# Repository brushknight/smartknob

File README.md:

# ⚠️⚠️⚠️ This repo is archived, check for updates at [@seedlabs-it](https://github.com/seedLabs-it/) 

# SmartKnob
SmartKnob is an open-source input device with software-configurable endstops and virtual detents.

A brushless gimbal motor is paired with a magnetic encoder to provide closed-loop torque feedback control, making it
possible to dynamically create and adjust the feel of detents and endstops.

Join the [Discord community](https://discord.gg/5jyhjcbTnR) to discuss the project with others, show off your build, or help answer each others' questions!

# Designs

## SmartKnob View
The "SmartKnob View" is the premium SmartKnob experience with an integrated display shown in my [demo video](https://www.youtube.com/watch?v=ip641WmY4pA). Under active development.

🎉 **Motors are [now available](https://www.sparkfun.com/products/20441)!** If you've been following this project,
you'll know that the recommended motors went out of stock nearly immediately after it was published.
Thanks to [the community](https://github.com/scottbez1/smartknob/issues/16#issuecomment-1094482805%5D), we were able to
identify the likely original manufacturer, and recently SparkFun Electronics has been getting them produced and regularly
[stocking them](https://www.sparkfun.com/products/20441)! (However, they've been selling out quickly each time they restock, so definitely sign up for backorder notifications if they're out of stock when you check). Thanks to everyone who helped search and investigate different
motor options along the way!

Features:
 - 240x240 round LCD ("GC9A01"), protected by 39.5mm watch glass on rotor
 - BLDC gimbal motor, with a hollow shaft for mechanically & electrically connecting the LCD
 - Powered by ESP32-PICO-V3-02 (Lilygo TMicro32 Plus module)
 - PCB flexure and SMD resistors used as strain gauges for press detection (haptic feedback provided via the motor)
 - 8 side-firing RGB LEDs (SK6812-SIDE-A) illuminate ring around the knob
 - USB-C (2.0) connector for 5V power and serial data/programming (CH340)
 - VEML7700 ambient light sensor for automatic backlight & LED intensity adjustment
 - Versatile back plate for mounting - use either 4x screws, or 2x 3M medium Command strips (with cutouts for accessing removal tabs after installation)
 - Front cover snaps on for easy access to the PCB

**Current status:** Not recommended for general use, but may be a fun project for an advanced electronics hobbyist.

### Demo video

### How it works

### 3D CAD

Latest Fusion 360 Model: https://a360.co/3BzkU0n

#### DEMO: video editor timeline control

If you edit audio/video, imagine having a jog wheel where you could _feel_ the clip boundaries as you scrolled through the timeline. Then switch to playback speed control, with a wheel that's spring-loaded to return to "paused," with snaps at 1x, 2x, 4x, etc. The SmartKnob can do this; it just needs some software integrations to be written. Check out a demo using a SmartKnob prototype to control a mock video timeline:

(you can actually try this demo yourself if you've already built a SmartKnob; plug it in over USB and go to https://scottbez1.github.io/smartknob/)

### Build your own?

While this is a "DIY" open-source project, it is not yet a mature plug-and-play project. If you intend to build your own, note that it requires advanced soldering experience to build - very small-pitch surface-mount soldering is required (reflow or hot air recommended), and assembly is quite time-consuming and delicate. Please go into it with the expectation that you will almost certainly need to be able to troubleshoot some hardware and firmware issues yourself - I recommend reviewing/understanding the schematics and basic firmware before jumping in!

More documentation on the BOM and what parts you need to order is coming in the future - thanks so much for your interest! Follow me on [Twitter](https://twitter.com/scottbez1) for the latest updates on this and other projects.

View the latest auto-generated (untested) [Base PCB Interactive BOM](https://smartknob-artifacts.s3.us-west-1.amazonaws.com/master/electronics/view_base-ibom.html) and [Screen PCB Interactive BOM](https://smartknob-artifacts.s3.us-west-1.amazonaws.com/master/electronics/view_screen-ibom.html) (or, the combined [BOM csv](https://smartknob-artifacts.s3.us-west-1.amazonaws.com/master/electronics/view_base-bom.csv)) for electronics/hardware parts list. ⚠️ These are auto-generated from the latest untested revision on GitHub. For tested/stable/recommended artifacts, use a [release](https://github.com/scottbez1/smartknob/releases) instead.

A few miscellaneous notes in the meantime:

 - There's limited space inside the LCD mount for wiring, and 8 wires need to fit through the hole in the center. I used 30 AWG wire-wrapping wire. Enamel-coated wire would probably work too.
 - Older versions of the design (as seen in the videos) used glued-on BF350-3AA strain gauges to detect presses; in v0.5 these were replaced with footprints for SMD resistors, which exhibit similar properties when stretched/compressed and are much easier to assemble. 
 - The TMC6300 is _tiny_ and has a bottom pad, so I would seriously consider getting a stencil along with the PCB order. Even with the stencil I needed to manually clean up some bridging afterward; I _highly_ recommend Chip Quik NC191 gel flux, available on [Amazon](https://amzn.to/3MGDSr5) (or use this [non-affiliate link](https://www.amazon.com/Smooth-Flow-No-Clean-syringe-plunger/dp/B08KJPG3NZ) instead) or from your electronics distributor of choice. Flux is also very helpful when soldering the LCD ribbon cable to to screen PCB.
 - For breadboard prototyping, the [TMC6300-BOB](https://www.trinamic.com/support/eval-kits/details/tmc6300-bob/) or SparkFun's [TMC6300 driver board](https://www.sparkfun.com/products/21867) are awesome and way easier to work with than the bare chip if you just want to play around with low current BLDC motors
 - For AliExpress purchases: I highly recommend **only** using AliExpress Standard Shipping (purchasing in the US). I have had multiple purchases take months or never get delivered when purchased with Cainiao or other low cost shipping options, whereas AliExpress Standard is very reliable and generally faster in my experience.
 - Make sure to check the [open issues](https://github.com/scottbez1/smartknob/issues) - this design is not yet "stable", so beware that everything may not go smoothly.

Future plans:
 - consider switch to using an ESP32-S3-MINI-1 module
 - get wifi configured and working (probably MQTT?). Currently memory is an issue with the full display framebuffer sprite. PSRAM might fix this (requires newer ESP-IDF & unreleased Arduino core, and from a brief test I got horrible performance with PSRAM enabled), or the next item might help reduce memory:
 - migrate to LVGL, for better display rendering and easy support for menus, etc. Shouldn't require a full 240x240x24b framebuffer in memory, freeing some for wifi, etc.
 - Home Assistant integration, or other real-world applications
 - ???
 - [Profit](https://github.com/sponsors/scottbez1/) 😉

#### Already built one?
Check out the [firmware/software documentation](https://paper.dropbox.com/doc/SmartKnob-firmware-and-software--B_oWj~L1dXqHgAqqYmhwwuqzAg-VUb9nq7btuhnHw5KlgJIH)
for tips on getting it programmed and hooking it up to your own software integrations.

If you've already uploaded the standard firmware and gone through the calibration process (see guide linked above if you don't know what this means),
go to https://scottbez1.github.io/smartknob/ to try out an interactive web-based demo that uses Web Serial to talk to a SmartKnob that's plugged into your
computer's USB port!

#### Base PCB

Ordering notes: use white soldermask, for reflecting light from RGB LED ring around the knob. Should be 1.2mm thick (not "standard" 1.6mm).

If you are ordering a stencil for solder paste from JLCPCB and plan to apply paste by hand (as
[shown in the video](https://youtu.be/Q76dMggUH1M?t=372)) without a stencil frame/machine, make sure to select
**"Customized size"** and enter smaller dimensions (e.g. 100mm x 100mm) to avoid getting a much larger stencil than you
need. This will also likely reduce the cost of shipping substantially! Also, select only the **Top** side; the bottom
only has 2 SMT components - the motor connector and VEML7700 ALS - so it's not worth getting a stencil for that.

Latest auto-generated (untested and likely broken!) artifacts⚠️:

[Schematic](https://smartknob-artifacts.s3.us-west-1.amazonaws.com/master/electronics/view_base-schematic.pdf)

[Interactive BOM](https://smartknob-artifacts.s3.us-west-1.amazonaws.com/master/electronics/view_base-ibom.html)

[PCB Packet](https://smartknob-artifacts.s3.us-west-1.amazonaws.com/master/electronics/view_base-pcb-packet.pdf)

[Gerbers](https://smartknob-artifacts.s3.us-west-1.amazonaws.com/master/electronics/view_base-jlc/gerbers.zip)

⚠️ For tested/stable/recommended artifacts, use a [release](https://github.com/scottbez1/smartknob/releases) instead.

#### Screen PCB

Ordering notes: Must be 1.2mm thick (not "standard" 1.6mm) per mechanical design. (The PCB silkscreen mentions 0.6mm thickness - this is the thickness of the **VHB tape** for adhering the LCD; the PCB should be 1.2mm thick)

There are few enough components on the Screen PCB that I chose to hand-solder them rather than reflow with solder paste
and a stencil, but if you order a stencil, see the note above about selecting a "Customized size" to be easier to
handle and save on shipping. Also make sure to select the **Bottom** side only; all the components are on the bottom
side of the screen PCB.

Latest auto-generated (untested and likely broken!) artifacts⚠️:

[Schematic](https://smartknob-artifacts.s3.us-west-1.amazonaws.com/master/electronics/view_screen-schematic.pdf)

[Interactive BOM](https://smartknob-artifacts.s3.us-west-1.amazonaws.com/master/electronics/view_screen-ibom.html)

[PCB Packet](https://smartknob-artifacts.s3.us-west-1.amazonaws.com/master/electronics/view_screen-pcb-packet.pdf)

[Gerbers](https://smartknob-artifacts.s3.us-west-1.amazonaws.com/master/electronics/view_screen-jlc/gerbers.zip)

⚠️ For tested/stable/recommended artifacts, use a [release](https://github.com/scottbez1/smartknob/releases) instead.

#### Printed parts
You will need six printed parts. The current stable designs can be found as STL assets in the [v185 mechanical release](https://github.com/scottbez1/smartknob/releases/tag/releases%2Fmechanical%2Fv185-dummy-tag) or you can export the latest untested designs from the CAD model by opening it in Fusion 360: https://a360.co/3BzkU0n

The parts can _probably_ be FDM 3D printed with a well-tuned printer, but the parts shown in videos/photos were MJF printed in nylon for tight tolerances and better surface finish. 

If you wanted a simpler build, you could omit the LCD and just merge the knob + glass from the model into a single STL to get a closed-top knob.

Export and print the following 6 parts:
* `Enclosure`
* `Knob` (RotorAssembly->KnobAssembly->Knob)
* `ScreenPlatform`
* `RotorSpacer` (RotorAssembly->RotorSpacer)
* `MountBase`
* `BackPlate`

⚠️ If you opt to go for MJF Nylon printing from JLCPCB, their system may complain about `< 0.8mm wall thickness detected` on the `MountBase`, `ScreenPlatform` and `RotorSpacer` parts. This appears to be a false positive, possibly on some of the print tapers. You should be able to ignore this, as all print orders at JLCPCB are subject to a final manual review, and they will contact you by email if there are any job-stopping issues or risks with your prints.

## NanoFOC (3rd party)
If you're looking to tinker with FOC/haptic feedback, but don't want to build a full SmartKnob View yourself, I can
recommend the NanoFOC DevKit++, an [open-source design](https://github.com/katbinaris/nanofoc_devkit) made and
[sold](https://store.binaris.io/products/nanofoc-devkit) by a member of the SmartKnob community! It's super compact
and is a great testbed or core for building your own BLDC-based haptic input device.

The NanoFOC uses an ESP32-S3, and the SmartKnob firmware works on it out of the box; just select the `nanofoc`
environment in PlatformIO rather than the `view` environment when uploading.

# Frequently Asked Questions (FAQ)

### Can I use this cheap gimbal BLDC motor I found on AliExpress?

I can't stop you, but I will caution that **you probably won't be super happy with it** depending on your intended application.

Nearly every off-the-shelf BLDC gimbal motor that the community has tested (which is pretty much ALL the cheap ones you'll find on AliExpress, trust me) has
_moderate to severge cogging_. That means the motor wants to snap to certain positions by itself even when unpowered. This means you won't be able to get
completely smooth rotation when virtual detents are turned off, and the motor's cogging may interfere with or overpower the virtual detents, particularly if
you set them to lower strength or make then very fine-grained.

The recommended motor is definitely the best (i.e. lowest cogging) off-the-shelf motor we've come across so far, and is the only readily-available motor
that I would consider "good" for this application.

If you've found another motor that is completely smooth when unpowered, we'd LOVE to hear about it in the discord; if you're wondering about some cheap motor
you saw online, either just order one and try it for yourself, or ask about it in discord but don't be surprised (or offended) if the response you get is
something terse like "nope, no good".

### How much does it cost?

I wish I could tell you now, but I don't actually know off the top of my head. Check back soon - I've only built a few so far, which was the result of a bunch of tinkering and prototyping over an extended period, so I don't have all the expenses tallied up yet. Probably less than $200 in parts? But some items have gotten more expensive, and you may be limited by minimum order quantities or shipping charges from multiple separate suppliers.

### Does it work with XYZ?

Not yet, regardless of whatever "XYZ" you're thinking of. So far I've only implemented enough firmware for the demo shown in the video, so you can't actually use it for anything productive yet. The basic detent configuration API is there, but not much else. Lots of firmware work remains to be done. If you build one, I'd love your help adding support for "XYZ" though!

### Can I buy one as a kit or already assembled?

Probably not? Or at least, I don't have any immediate plans to sell them myself. It's not that I don't want you to be happy, but hardware is a hard business and I just work on this stuff in my free time.

It's open source with a fairly permissive license though, so in theory anyone could start offering kits/assemblies. If someone does go down that route of selling them, note that attribution is
 _required_ (and I wouldn't say no to [royalties/tips/thanks](https://github.com/sponsors/scottbez1/) if you're in a giving mood 🙂).

# Firmware and Software
More extensive documentation of the firmware and software (and how to get started) can be found in the dedicated [SmartKnob Firmware and Software Guide](https://paper.dropbox.com/doc/SmartKnob-firmware-and-software--Byho6npe9XvZLZLxJ_8bK5TqAg-VUb9nq7btuhnHw5KlgJIH#:h2=Calibration)

## General Component Info

### Magnetic encoders

#### MT6701 (MagnTek)
Excellent sensor at a reasonable price - highly recommended. Less noisy than TLV493D, and more responsive (control loop is more stable) using SSI.

 - Lots of IO options - SSI, I2C, and ABZ - should offer good response latency
 - SSI includes CRC to validate data
 - No power-down or low-power options - may not be ideal for battery-powered devices
 - Not available from US distributors (Mouser, Digi-Key)

[Datasheet](http://www.magntek.com.cn/upload/MT6701_Rev.1.5.pdf)

[Ordering (LCSC)](https://lcsc.com/product-detail/Angle-Linear-Position-Sensors_Magn-Tek-MT6701CT-STD_C2856764.html)

#### TLV493D (Infineon)
Not used in the SmartKnob view, but a common/popular magnetic encoder in general. It's a mediocre choice for a haptic feedback implementation. Easy to prototype with using [Adafruit's QWIIC breakout board](https://www.adafruit.com/product/4366).

In my testing, it's noisy, requiring filtering/smoothing that can slow responsiveness, hurting control loop stability. Or, with less filtering, the noise
can easily be "amplified" by the derivative component in the PID motor torque controller, causing audible (and tactile) humming/buzzing.

But the bigger issue is that there is apparently a known silicon issue that causes the internal ADC to sometimes completely lock up, requiring a full reset and re-configuration, which can cause delays/gaps in data! See section
5.6 in the [User Manual](https://www.infineon.com/dgdl/Infineon-TLV493D-A1B6_3DMagnetic-UM-v01_03-EN.pdf?fileId=5546d46261d5e6820161e75721903ddd)

    In the Master Controlled Mode (MCM) or the Fast Mode (FM) the ADC conversion may hang up. A hang up can
    be detected by:
     - Frame Counter (FRM) counter stucks and does not increment anymore.

In my experience testing 4 different Adafruit breakout boards, 2 of them (50%) regularly exhibit this lockup behavior within a minute or two of use. It is possible to detect and auto-reset (and there is code in the project to do so), but it is slow and may cause undesirable jumps/delays if the sensor locks up often.

[Datasheet](https://www.mouser.com/datasheet/2/196/Infineon_TLV493D_A1B6_DataSheet_v01_10_EN-1227967.pdf)

#### AS5600 (AMS)
A mediocre choice. Cheap breakout boards are readily available.

In my testing, it's fairly noisy (anecdotally, noisier than the TLV493d), requiring filtering/smoothing that can slow responsiveness, hurting control loop stability. Additionally, it saturates at a lower magnetic field strength than other sensors I tested, requiring a significant air gap (8-10mm) when used with a strong neodymium diametric magnet like [Radial Magnets 8995](https://www.digikey.com/en/products/detail/radial-magnets-inc/8995/5126077).

[Datasheet](https://ams.com/documents/20143/36005/AS5600_DS000365_5-00.pdf)

### Motor drivers
#### TMC6300-LA
This is a relatively new IC and it's a perfect match! There generally aren't any other drivers (with integrated fets) that meet the requirements for the low-voltage and low-current motors used in this project (DRV8316 might work, but has not been tested).

Highlights:
 - 2-11V DC motor supply input
 - Up to 1.2A RMS
 - Tiny (3x3mm QFN)

 [Datasheet](https://www.trinamic.com/fileadmin/assets/Products/ICs_Documents/TMC6300_datasheet_rev1.07.pdf)

 [Product page](https://www.trinamic.com/products/integrated-circuits/details/tmc6300-la/)

### Motors
#### 32mm Rotor, Hollow Shaft, Diametric magnet

- 32mm rotor
- 15mm overall height (including magnet), 12.75mm height w/o magnet, 9mm rotor height
- low/zero cogging - excellent for completely smooth input
- 5.9mm hollow shaft
- built-in diametric magnet for encoder
- Proven option

This is overall the easiest motor to get started with. Low cogging and a built-in diametric magnet are great!

Available [from SparkFun](https://www.sparkfun.com/products/20441)!

# Acknowledgements
This project was greatly inspired by Jesse Schoch's video "[haptic textures and virtual detents](https://www.youtube.com/watch?v=1gPQfDkX3BU)" and the
corresponding [discussion in the SimpleFOC community](https://community.simplefoc.com/t/haptic-textures/301). Seriously, this project wouldn't exist if not for that video - thank you Jesse!

# License

This project is licensed under Apache v2 (software, electronics, documentation) and Creative Commons Attribution 4.0 (hardware/mechanical) (see [LICENSE.txt](LICENSE.txt) and [Creative Commons](https://creativecommons.org/licenses/by/4.0/)).

    Copyright 2022 Scott Bezek
    
    Licensed under the Apache License, Version 2.0 (the "License");
    you may not use this file except in compliance with the License.
    You may obtain a copy of the License at
    
        http://www.apache.org/licenses/LICENSE-2.0
    
    Unless required by applicable law or agreed to in writing, software
    distributed under the License is distributed on an "AS IS" BASIS,
    WITHOUT WARRANTIES OR CONDITIONS OF ANY KIND, either express or implied.
    See the License for the specific language governing permissions and
    limitations under the License.

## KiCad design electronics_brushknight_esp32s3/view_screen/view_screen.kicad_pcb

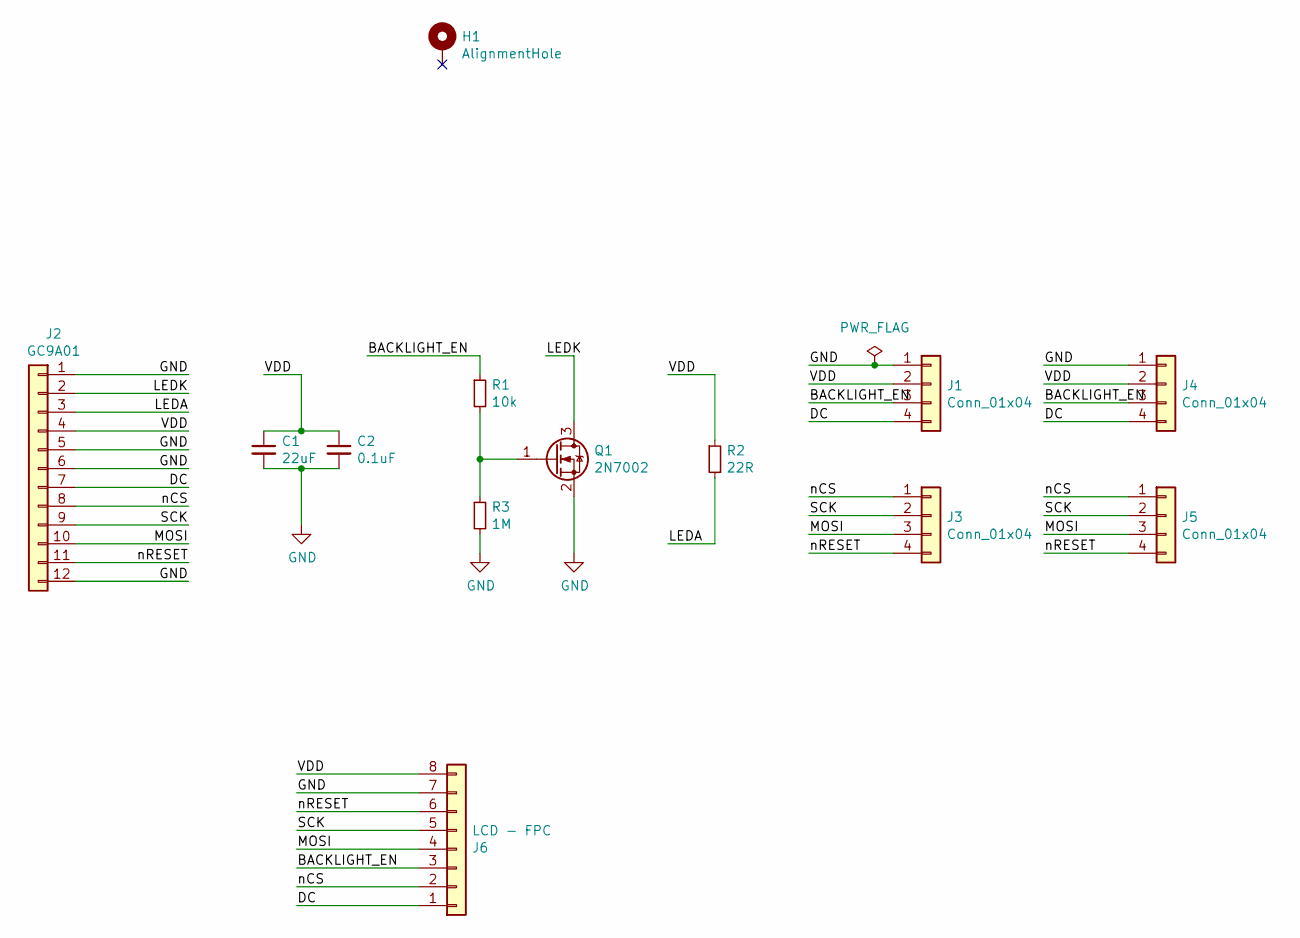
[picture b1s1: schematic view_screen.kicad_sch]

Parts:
C1: 22uF; C_0805_2012Metric; Digikey 1276-CL21A226MAYNNNECT-ND
C2: 0.1uF; C_0603_1608Metric; Digikey 1276-1935-1-ND
H1: AlignmentHole; AlignmentHole_1.6
J1, J3, J4, J5: Conn_01x04; SolderPads_2mm_4
J2: GC9A01; GC9A01Round1.28; Digikey N/A
J6: LCD - FPC; Amphenol FCI FPC 8 pin 0.5 pitch
Q1: 2N7002; SOT-23; Digikey 2N7002H6327XTSA2CT-ND
R1: 10k; R_0603_1608Metric; Digikey RMCF0603JT10K0CT-ND
R2: 22R; R_0603_1608Metric; Digikey RMCF0603JT22R0CT-ND
R3: 1M; R_0603_1608Metric; Digikey RMCF0603JT1M00CT-ND

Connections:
/BACKLIGHT_EN: J1.3, J4.3, J6.3, R1.1
/DC: J1.4, J2.7, J4.4, J6.1
/LEDA: J2.3, R2.2
/LEDK: J2.2, Q1.3 (D)
/MOSI: J2.10, J3.3, J5.3, J6.4
/SCK: J2.9, J3.2, J5.2, J6.5
/VDD: C1.1, C2.1, J1.2, J2.4, J4.2, J6.8, R2.1
/nCS: J2.8, J3.1, J5.1, J6.2
/nRESET: J2.11, J3.4, J5.4, J6.6
GND: C1.2, C2.2, J1.1, J2.1, J2.5, J2.6, J2.12, J4.1, J6.7, Q1.2 (S), R3.2
unnamed: Q1.1 (G), R1.2, R3.1

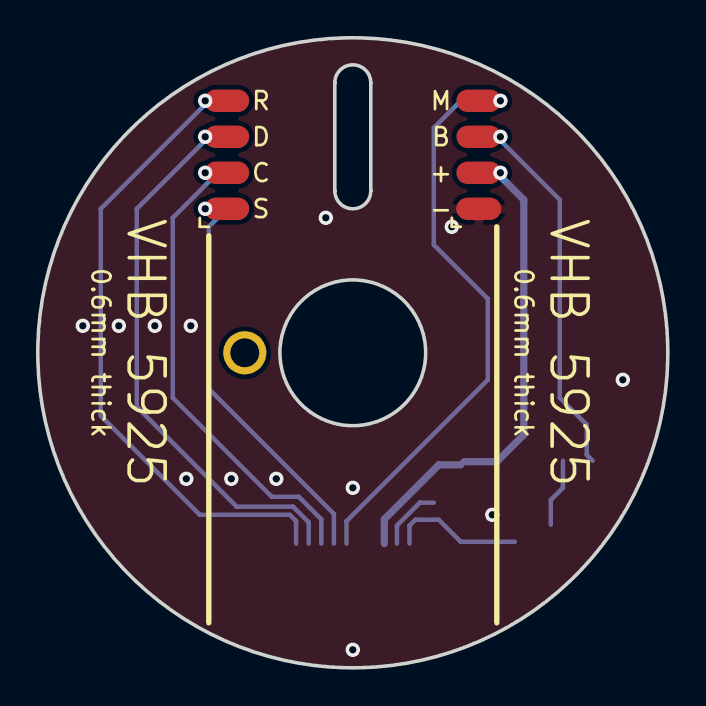
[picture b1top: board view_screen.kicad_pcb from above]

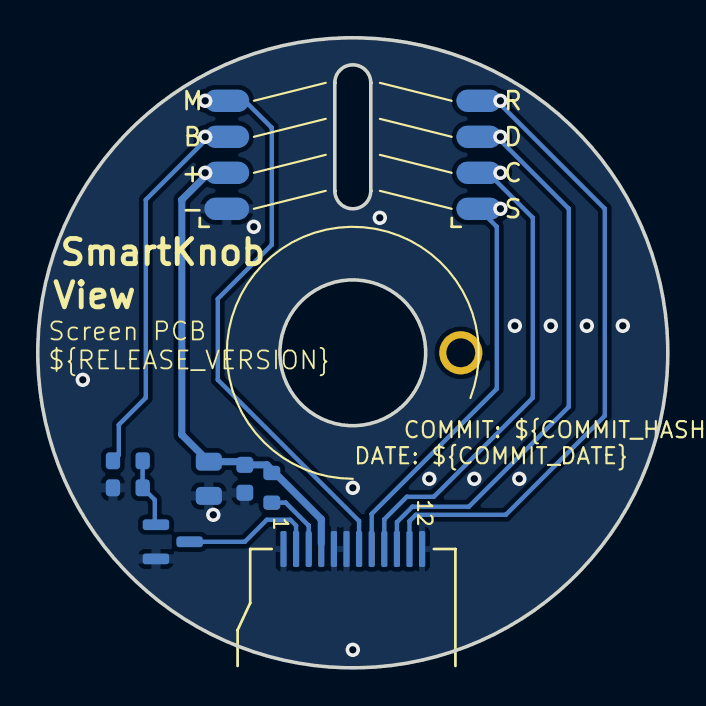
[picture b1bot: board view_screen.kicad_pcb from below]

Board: 2 copper layers, 35.0 x 35.0 mm, 12 parts (9 on the bottom side), 11 nets.

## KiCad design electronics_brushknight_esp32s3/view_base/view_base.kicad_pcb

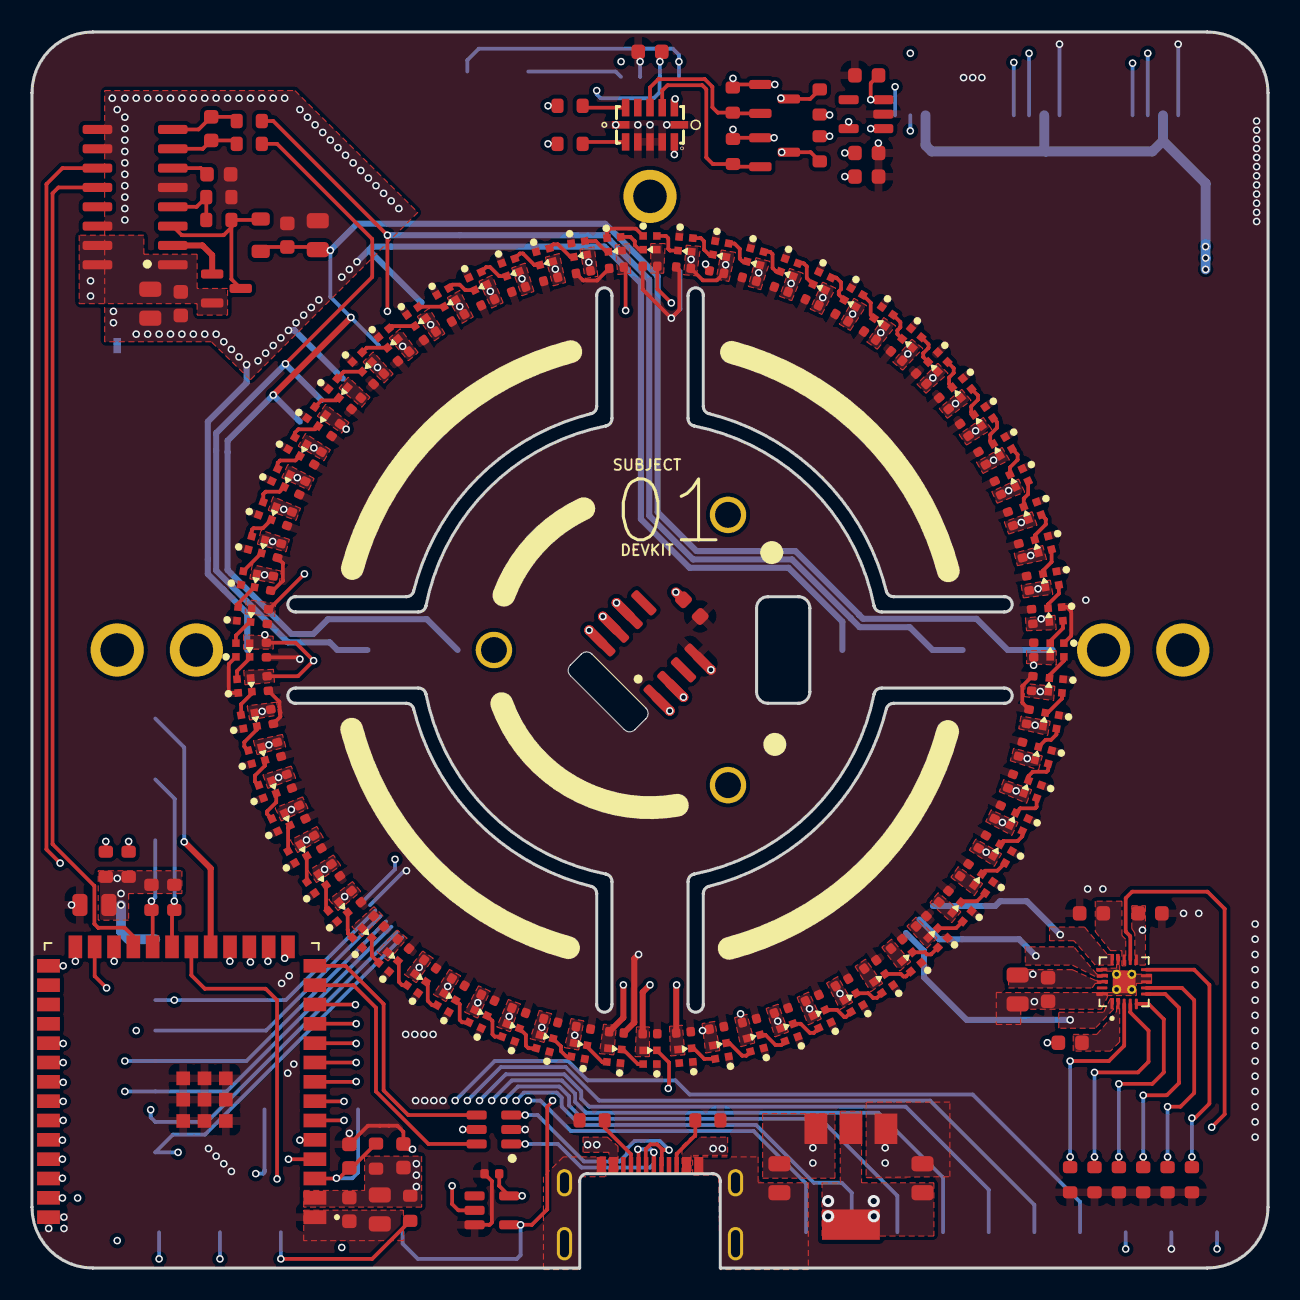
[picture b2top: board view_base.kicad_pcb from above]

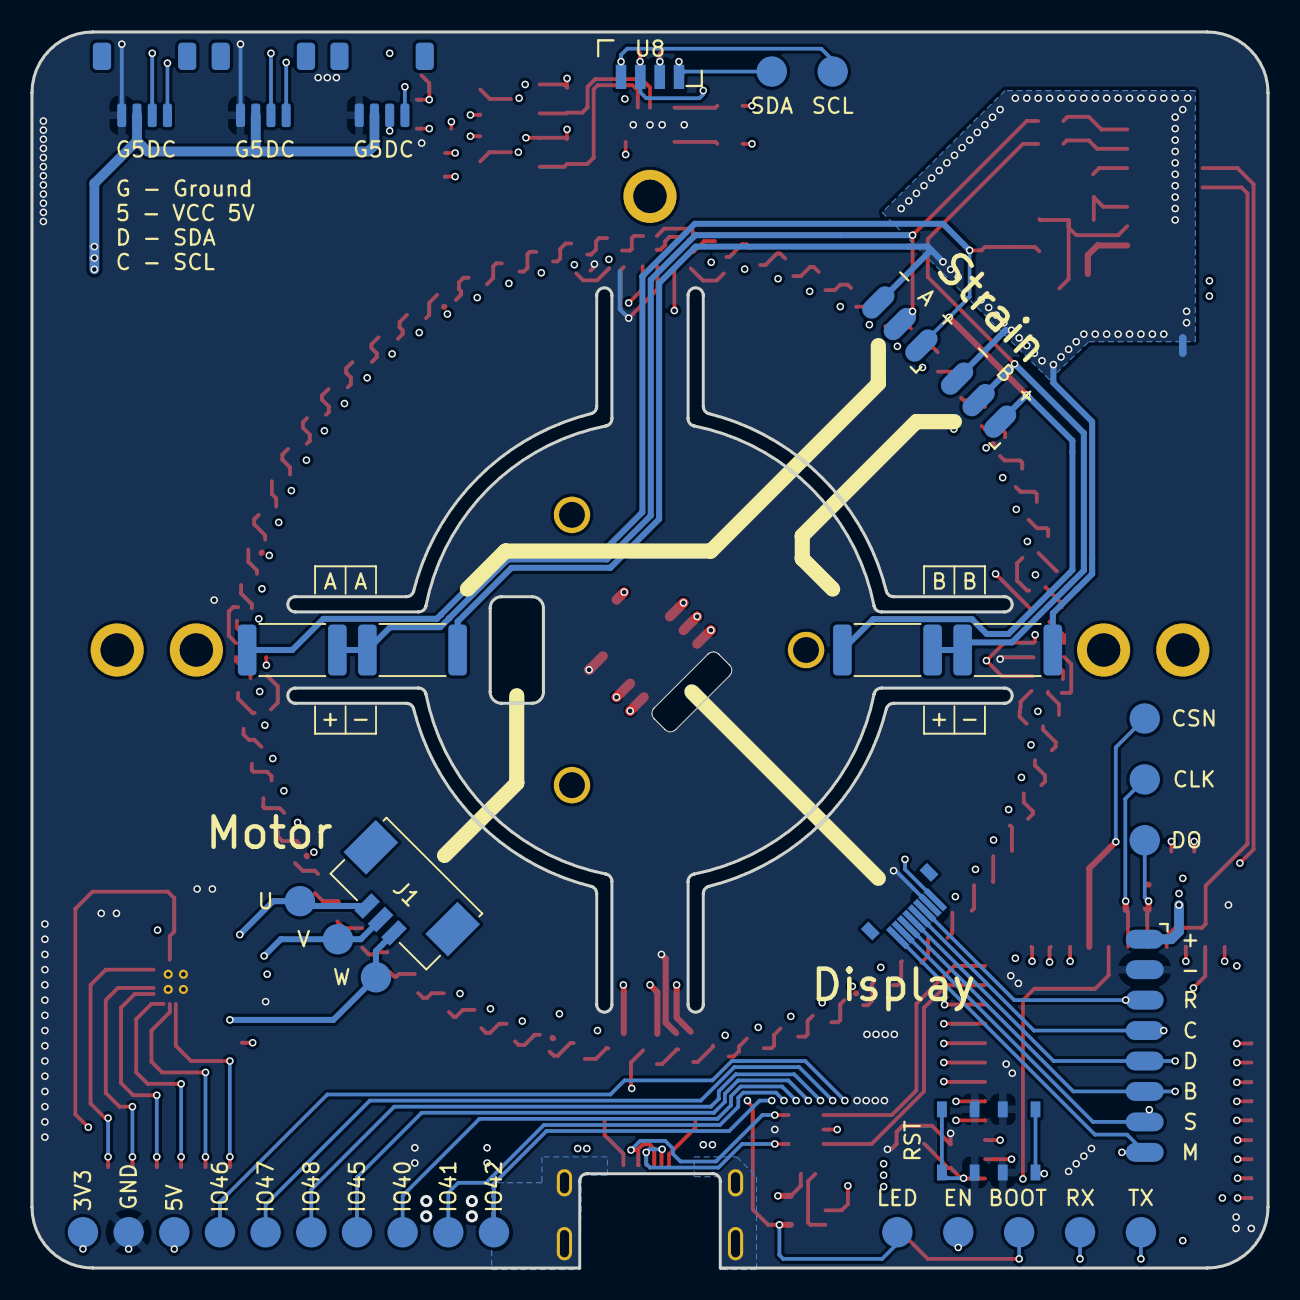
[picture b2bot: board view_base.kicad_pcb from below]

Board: 4 copper layers, 81.2 x 81.2 mm, 258 parts (39 on the bottom side), 133 nets.

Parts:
C1, C2, C3, C4, C5, C6, C7, C8, C11#2, C29, C30, C31, C32, C33, C34, C35, C36, C37, C38, C39, C40, C41, C42, C43, C44, C45, C46, C47, C48, C49, C50, C51, C52, C53, C54, C55, C56, C57, C58, C59, C60, C61, C62, C63, C64, C65, C66, C67, C68, C69, C70, C71, C72, C73, C74, C75, C76, C77, C79, C80, C81, C82, C88, C90, C92, C94, C95, C96, C97, C98, C99, C100, C101: 0.1uF; C_0402_1005Metric
C9, C10, C16, C18, C24, C26: 10uF; C_0805_2012Metric
C11, C12, C14, C15, C17, C19, C20, C21, C22, C23, C25, C27: 0.1uF; C_0603_1608Metric
C13: 22uF; C_0805_2012Metric
C28: 1uF; C_0603_1608Metric
C78, C83: 10uF; C_0603_1608Metric
C84: 100nF; C_0603_1608Metric
D9, D10, D11, D12, D13, D14, D15, D16, D17, D18, D19, D20, D21, D22, D23, D24, D25, D26, D27, D28, D29, D30, D31, D32, D33, D34, D35, D36, D37, D38, D39, D40, D41, D42, D43, D44, D45, D46, D47, D48, D49, D50, D51, D52, D53, D54, D55, D56, D57, D58, D59, D60, D61, D62, D63, D64, D65, D66, D67, D68, D69, D70, D71, D72, D73, D74, D75, D76, D77, D78, D79, D80: SK6805; LED_SK6812_EC15_1.5x1.5mm
H1, H2, H3: MotorHole; MountingHole_M1.6
H5, H6, H7: MountHole; MountingHole_2.2mm_M2_ISO7380_Pad_NonVirtual
H8, H9: AlignmentHole; MountingHole_2.2mm_M2_ISO7380_Pad_NonVirtual
J1: BLDC; 532610371
J2: USB_C_Receptacle_USB2.0; USB4510_NoPaste
J3: LCD; SolderPads_2mm_8
J4: A; SolderPads_2mm_3_STRAIN
J5: B; SolderPads_2mm_3_STRAIN
J6: LCD - FPC; Amphenol FCI FPC 8 pin 0.5 pitch
J7, J8, J9: Conn_01x04_Socket; JST_SH_SM04B-SRSS-TB_1x04-1MP_P1.00mm_Horizontal
L1: 3.3uH; L_0805_2012Metric
NT1: NetTie_2; NetTie-2_SMD_Pad0.5mm
Q1: MMBT4403; SOT-23
Q2, Q3: BSS138; SOT-23
R1, R2: 5.1k; R_0603_1608Metric
R3, R7, R8, R9, R10, R11, R12, R17, R28: 10k; R_0603_1608Metric
R4: 8.2k; R_0603_1608Metric
R5, R6: 100; R_0603_1608Metric
R13, R14, R15, R16: 2.2k; R_0603_1608Metric
R18, R19, R20, R21: 330; R_2512_6332Metric
R22, R23, R24, R25, R26, R27: 10K; R_0603_1608Metric
SW1: RST; SW_SPST_PTS810
SW2: Boot; SW_SPST_PTS810
TP1: 5V; TestPoint_Pad_D2.0mm_ValueSilk
TP2: 3V3; TestPoint_Pad_D2.0mm_ValueSilk
TP3: GND; TestPoint_Pad_D2.0mm_ValueSilk
TP4: SDA; TestPoint_Pad_D2.0mm_ValueSilk
TP5: SCL; TestPoint_Pad_D2.0mm_ValueSilk
TP6: U; TestPoint_Pad_D2.0mm_ValueSilk
TP7: V; TestPoint_Pad_D2.0mm_ValueSilk
TP8: W; TestPoint_Pad_D2.0mm_ValueSilk
TP9: CSN; TestPoint_Pad_D2.0mm_ValueSilk
TP10: CLK; TestPoint_Pad_D2.0mm_ValueSilk
TP11: DO; TestPoint_Pad_D2.0mm_ValueSilk
TP12: LED; TestPoint_Pad_D2.0mm_ValueSilk
TP13: EN; TestPoint_Pad_D2.0mm_ValueSilk
TP14: BOOT; TestPoint_Pad_D2.0mm_ValueSilk
TP15: TX; TestPoint_Pad_D2.0mm_ValueSilk
TP16: RX; TestPoint_Pad_D2.0mm_ValueSilk
TP17: IO40; TestPoint_Pad_D2.0mm_ValueSilk
TP18: IO41; TestPoint_Pad_D2.0mm_ValueSilk
TP19: IO42; TestPoint_Pad_D2.0mm_ValueSilk
TP20: IO45; TestPoint_Pad_D2.0mm_ValueSilk
TP21: IO46; TestPoint_Pad_D2.0mm_ValueSilk
TP22: IO47; TestPoint_Pad_D2.0mm_ValueSilk
TP23: IO48; TestPoint_Pad_D2.0mm_ValueSilk
U1: MT6701-CT; SOIC-8_3.9x4.9mm_P1.27mm
U2: USBLC6-2SC6; SOT-23-6
U3: VL53L0CXV0DH_1; LGA12_1
U4: HX711; SOIC-16_3.9x9.9mm_P1.27mm
U5: TMC6300; QFN-20-1EP_3x3mm_P0.4mm_EP1.65x1.65mm_ThermalVias_LargerVia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
U6: LP5907MFX-2.8; SOT-23-5
U7: SN74LV1T34DBV; SOT-23-5
U8: VEML7700; VEML7700-TOP
U9: TS1117BCW33_RPG; SOT-223-3_TabPin2_GndOutIn
U10: ESP32-S3-WROOM-1-N8R8; XCVR_ESP32S3WROOM1N8R8U
Z6, Z7, Z8: RotorScrew (BOM-only); bom_only_no_pin
Z9: WatchGlass39.5mm; bom_only_no_pin
Z10: BLDCMotor; bom_only_no_pin

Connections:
+2V8: C83.2, C84.2, Q2.1 (G), Q3.1 (G), R22.2, R23.2, R24.2, R25.2, U3.1 (AVDDVCSEL), U3.11 (AVDD), U6.5 (OUT)
+3V3: C10.1, C11.1, C12.1, C16.1, C17.1, C20.1, C24.1, C25.1, C26.1, C27.1, C78.2, J3.1, J6.1, Q1.2 (E), R13.1, R14.1, R15.1, R16.2, R17.1, R26.2, R27.2, R28.1, TP2.1, U1.1 (VDD), U1.2 (MODE), U4.1 (VSUP), U4.15 (RATE), U4.16 (DVDD), U5.11 (VIO/~STDBY), U6.1 (IN), U6.3 (EN), U8.2 (VDD), U9.2 (Output), U10.2 (3V3)
+5V: C1.1, C2.1, C3.1, C4.1, C5.1, C6.1, C7.1, C8.1, C9.1, C11#2.1, C13.1, C14.1, C15.1, C29.1, C30.1, C31.1, C32.1, C33.1, C34.1, C35.1, C36.1, C37.1, C38.1, C39.1, C40.1, C41.1, C42.1, C43.1, C44.1, C45.1, C46.1, C47.1, C48.1, C49.1, C50.1, C51.1, C52.1, C53.1, C54.1, C55.1, C56.1, C57.1, C58.1, C59.1, C60.1, C61.1, C62.1, C63.1, C64.1, C65.1, C66.1, C67.1, C68.1, C69.1, C70.1, C71.1, C72.1, C73.1, C74.1, C75.1, C76.1, C77.1, C79.1, C80.1, C81.1, C82.1, C88.1, C90.1, C92.1, C94.1, C95.1, C96.1, C97.1, C98.1, C99.1, C100.1, C101.1, D9.3 (VDD), D10.3 (VDD), D11.3 (VDD), D12.3 (VDD), D13.3 (VDD), D14.3 (VDD), D15.3 (VDD), D16.3 (VDD), D17.3 (VDD), D18.3 (VDD), D19.3 (VDD), D20.3 (VDD), D21.3 (VDD), D22.3 (VDD), D23.3 (VDD), D24.3 (VDD), D25.3 (VDD), D26.3 (VDD), D27.3 (VDD), D28.3 (VDD), D29.3 (VDD), D30.3 (VDD), D31.3 (VDD), D32.3 (VDD), D33.3 (VDD), D34.3 (VDD), D35.3 (VDD), D36.3 (VDD), D37.3 (VDD), D38.3 (VDD), D39.3 (VDD), D40.3 (VDD), D41.3 (VDD), D42.3 (VDD), D43.3 (VDD), D44.3 (VDD), D45.3 (VDD), D46.3 (VDD), D47.3 (VDD), D48.3 (VDD), D49.3 (VDD), D50.3 (VDD), D51.3 (VDD), D52.3 (VDD), D53.3 (VDD), D54.3 (VDD), D55.3 (VDD), D56.3 (VDD), D57.3 (VDD), D58.3 (VDD), D59.3 (VDD), D60.3 (VDD), D61.3 (VDD), D62.3 (VDD), D63.3 (VDD), D64.3 (VDD), D65.3 (VDD), D66.3 (VDD), D67.3 (VDD), D68.3 (VDD), D69.3 (VDD), D70.3 (VDD), D71.3 (VDD), D72.3 (VDD), D73.3 (VDD), D74.3 (VDD), D75.3 (VDD), D76.3 (VDD), D77.3 (VDD), D78.3 (VDD), D79.3 (VDD), D80.3 (VDD), J2.A4 (VBUS), J2.A9 (VBUS), J2.B4 (VBUS), J2.B9 (VBUS), J7.3, J8.3, J9.3, TP1.1, U2.5 (VBUS), U5.18 (VS), U7.5 (VCC), U9.3 (Input)
/ESP32_BOOT: R28.2, SW2.1, TP14.1, U10.27 (IO0)
/ESP32_EN: C28.1, R17.2, SW1.1, TP13.1, U10.3 (EN)
/ESP_USB_D+: U2.4 (I/O2), U10.14 (IO20)
/ESP_USB_D-: U2.6 (I/O1), U10.13 (IO19)
/LCD_BACKLIGHT: J3.6, J6.6, U10.5 (IO5)
/LCD_CMD: J3.8, J6.8, U10.38 (IO2)
/LCD_CS: J3.7, J6.7, U10.17 (IO9)
/LCD_DATA: J3.5, J6.5, U10.15 (IO3)
/LCD_RST: J3.3, J6.3, U10.18 (IO10)
/LCD_SCK: J3.4, J6.4, U10.4 (IO4)
/LED_DATA_3V3: U7.2 (A), U10.20 (IO12)
/LED_DATA_5V: D9.2 (DIN), TP12.1, U7.4 (Y)
/MAG_CLK: R16.1, TP10.1, U1.7 (B/V/SCL/CLK), U10.21 (IO13)
/MAG_CSN: TP9.1, U1.8 (Z/W/CSN), U10.19 (IO11)
/MAG_DO: R15.2, TP11.1, U1.6 (A/U/SDA/DO), U10.22 (IO14)
/STRAIN_DO: U4.12 (DOUT), U10.23 (IO21)
/STRAIN_E+: C18.1, C19.1, J4.1, J5.1, L1.2, R18.1, R20.2
/STRAIN_S+: J4.2, R6.1, R18.2, R19.1
/STRAIN_S-: J5.2, R5.2, R20.1, R21.2
/STRAIN_SCK: U4.11 (PD_SCK), U10.39 (IO1)
/TMC_DIAG: U5.12 (DIAG), U10.6 (IO6)
/TMC_UH: R7.1, U5.3 (UH), U10.12 (IO8)
/TMC_UL: R10.1, U5.6 (UL), U10.9 (IO16)
/TMC_VH: R8.1, U5.4 (VH), U10.11 (IO18)
/TMC_VL: R12.1, U5.10 (VL), U10.7 (IO7)
/TMC_WH: R9.1, U5.5 (WH), U10.10 (IO17)
/TMC_WL: R11.1, U5.7 (WL), U10.8 (IO15)
/USB_CC1: J2.A5 (CC1), R1.1
/USB_CC2: J2.B5 (CC2), R2.1
/USB_D+: J2.A6 (D+), J2.B6 (D+), U2.3 (I/O2)
/USB_D-: J2.A7 (D-), J2.B7 (D-), U2.1 (I/O1)
/USB_SERIAL_RXI: TP15.1, U10.37 (TXD0)
/USB_SERIAL_TXO: TP16.1, U10.36 (RXD0)
GND: C1.2, C2.2, C3.2, C4.2, C5.2, C6.2, C7.2, C8.2, C9.2, C10.2, C11.2, C11#2.2, C13.2, C14.2, C17.2, C20.2, C21.2, C24.2, C25.2, C26.2, C27.2, C28.2, C29.2, C30.2, C31.2, C32.2, C33.2, C34.2, C35.2, C36.2, C37.2, C38.2, C39.2, C40.2, C41.2, C42.2, C43.2, C44.2, C45.2, C46.2, C47.2, C48.2, C49.2, C50.2, C51.2, C52.2, C53.2, C54.2, C55.2, C56.2, C57.2, C58.2, C59.2, C60.2, C61.2, C62.2, C63.2, C64.2, C65.2, C66.2, C67.2, C68.2, C69.2, C70.2, C71.2, C72.2, C73.2, C74.2, C75.2, C76.2, C77.2, C78.1, C79.2, C80.2, C81.2, C82.2, C83.1, C84.1, C88.2, C90.2, C92.2, C94.2, C95.2, C96.2, C97.2, C98.2, C99.2, C100.2, C101.2, D9.1 (VSS), D10.1 (VSS), D11.1 (VSS), D12.1 (VSS), D13.1 (VSS), D14.1 (VSS), D15.1 (VSS), D16.1 (VSS), D17.1 (VSS), D18.1 (VSS), D19.1 (VSS), D20.1 (VSS), D21.1 (VSS), D22.1 (VSS), D23.1 (VSS), D24.1 (VSS), D25.1 (VSS), D26.1 (VSS), D27.1 (VSS), D28.1 (VSS), D29.1 (VSS), D30.1 (VSS), D31.1 (VSS), D32.1 (VSS), D33.1 (VSS), D34.1 (VSS), D35.1 (VSS), D36.1 (VSS), D37.1 (VSS), D38.1 (VSS), D39.1 (VSS), D40.1 (VSS), D41.1 (VSS), D42.1 (VSS), D43.1 (VSS), D44.1 (VSS), D45.1 (VSS), D46.1 (VSS), D47.1 (VSS), D48.1 (VSS), D49.1 (VSS), D50.1 (VSS), D51.1 (VSS), D52.1 (VSS), D53.1 (VSS), D54.1 (VSS), D55.1 (VSS), D56.1 (VSS), D57.1 (VSS), D58.1 (VSS), D59.1 (VSS), D60.1 (VSS), D61.1 (VSS), D62.1 (VSS), D63.1 (VSS), D64.1 (VSS), D65.1 (VSS), D66.1 (VSS), D67.1 (VSS), D68.1 (VSS), D69.1 (VSS), D70.1 (VSS), D71.1 (VSS), D72.1 (VSS), D73.1 (VSS), D74.1 (VSS), D75.1 (VSS), D76.1 (VSS), D77.1 (VSS), D78.1 (VSS), D79.1 (VSS), D80.1 (VSS), J2.A1 (GND), J2.A12 (GND), J2.B1 (GND), J2.B12 (GND), J2.S1 (SHIELD), J3.2, J6.2, J7.4, J8.4, J9.4, NT1.2, R1.2, R2.2, R7.2, R8.2, R9.2, R10.2, R11.2, R12.2, SW1.2, SW2.2, TP3.1, U1.4 (GND), U2.2 (GND), U3.2 (AVSSVCSEL), U3.3 (GND), U3.4 (GND2), U3.6 (GND3), U3.12 (GND4), U5.8 (GND), U5.9 (GND), U5.14 (GND), U5.16 (BRUV), U5.20 (BRW), U5.PAD, U6.2 (GND), U7.3 (GND), U8.3 (GND), U9.1 (GND), U10.1 (GND), U10.40 (GND), U10.41_1 (GND), U10.41_2 (GND), U10.41_3 (GND), U10.41_4 (GND), U10.41_5 (GND), U10.41_6 (GND), U10.41_7 (GND), U10.41_8 (GND), U10.41_9 (GND)
GNDA: C12.2, C16.2, C18.2, C19.2, C22.1, J4.3, J5.3, NT1.1, R4.2, R19.2, R21.1, U4.5 (AGND), U4.9 (INB-), U4.10 (INB+), U4.14 (XI)
unnamed: D9.4 (DOUT), D10.2 (DIN)
unnamed: D10.4 (DOUT), D11.2 (DIN)
unnamed: D11.4 (DOUT), D12.2 (DIN)
unnamed: D12.4 (DOUT), D13.2 (DIN)
unnamed: D13.4 (DOUT), D14.2 (DIN)
unnamed: D14.4 (DOUT), D15.2 (DIN)
unnamed: D15.4 (DOUT), D16.2 (DIN)
unnamed: D16.4 (DOUT), D17.2 (DIN)
unnamed: D17.4 (DOUT), D18.2 (DIN)
unnamed: D18.4 (DOUT), D19.2 (DIN)
unnamed: D19.4 (DOUT), D20.2 (DIN)
unnamed: D20.4 (DOUT), D21.2 (DIN)
unnamed: D21.4 (DOUT), D22.2 (DIN)
unnamed: D22.4 (DOUT), D23.2 (DIN)
unnamed: D23.4 (DOUT), D24.2 (DIN)
unnamed: D24.4 (DOUT), D25.2 (DIN)
unnamed: D25.4 (DOUT), D26.2 (DIN)
unnamed: D26.4 (DOUT), D27.2 (DIN)
unnamed: D27.4 (DOUT), D28.2 (DIN)
unnamed: D28.4 (DOUT), D29.2 (DIN)
unnamed: D29.4 (DOUT), D30.2 (DIN)
unnamed: D30.4 (DOUT), D31.2 (DIN)
unnamed: D31.4 (DOUT), D32.2 (DIN)
unnamed: D32.4 (DOUT), D33.2 (DIN)
unnamed: D33.4 (DOUT), D34.2 (DIN)
unnamed: D34.4 (DOUT), D35.2 (DIN)
unnamed: D35.4 (DOUT), D36.2 (DIN)
unnamed: D36.4 (DOUT), D37.2 (DIN)
unnamed: D37.4 (DOUT), D38.2 (DIN)
unnamed: D38.4 (DOUT), D39.2 (DIN)
unnamed: D39.4 (DOUT), D40.2 (DIN)
unnamed: D40.4 (DOUT), D41.2 (DIN)
unnamed: D41.4 (DOUT), D45.2 (DIN)
unnamed: D42.2 (DIN), D69.4 (DOUT)
unnamed: D42.4 (DOUT), D46.2 (DIN)
unnamed: D43.2 (DIN), D70.4 (DOUT)
unnamed: D43.4 (DOUT), D47.2 (DIN)
unnamed: D44.2 (DIN), D71.4 (DOUT)
unnamed: D44.4 (DOUT), D48.2 (DIN)
unnamed: D45.4 (DOUT), D49.2 (DIN)
unnamed: D46.4 (DOUT), D50.2 (DIN)
unnamed: D47.4 (DOUT), D51.2 (DIN)
unnamed: D48.4 (DOUT), D52.2 (DIN)
unnamed: D49.4 (DOUT), D53.2 (DIN)
unnamed: D50.4 (DOUT), D54.2 (DIN)
unnamed: D51.4 (DOUT), D55.2 (DIN)
unnamed: D52.4 (DOUT), D56.2 (DIN)
unnamed: D53.4 (DOUT), D57.2 (DIN)
unnamed: D54.4 (DOUT), D58.2 (DIN)
unnamed: D55.4 (DOUT), D59.2 (DIN)
unnamed: D56.4 (DOUT), D60.2 (DIN)
unnamed: D57.4 (DOUT), D61.2 (DIN)
unnamed: D58.4 (DOUT), D62.2 (DIN)
unnamed: D59.4 (DOUT), D63.2 (DIN)
unnamed: D60.4 (DOUT), D64.2 (DIN)
unnamed: D61.4 (DOUT), D65.2 (DIN)
unnamed: D62.4 (DOUT), D66.2 (DIN)
unnamed: D63.4 (DOUT), D67.2 (DIN)
unnamed: D64.4 (DOUT), D68.2 (DIN)
unnamed: D65.4 (DOUT), D69.2 (DIN)
unnamed: D66.4 (DOUT), D70.2 (DIN)
unnamed: D67.4 (DOUT), D71.2 (DIN)
unnamed: D68.4 (DOUT), D72.2 (DIN)
unnamed: D72.4 (DOUT), D73.2 (DIN)
unnamed: D73.4 (DOUT), D74.2 (DIN)
unnamed: D74.4 (DOUT), D75.2 (DIN)
unnamed: D75.4 (DOUT), D76.2 (DIN)
unnamed: D76.4 (DOUT), D77.2 (DIN)
unnamed: D77.4 (DOUT), D78.2 (DIN)
unnamed: D78.4 (DOUT), D79.2 (DIN)
unnamed: D79.4 (DOUT), D80.2 (DIN)
unnamed: J1.1, TP8.1, U5.1 (W)
unnamed: J1.2, TP7.1, U5.17 (V)
unnamed: J1.3, TP6.1, U5.15 (U)
unnamed: Q1.1 (B), U4.2 (BASE)
unnamed: L1.1, Q1.3 (C), R3.1, U4.3 (AVDD)
unnamed: R25.1, U3.7 (GPIO1)
unnamed: R22.1, U3.5 (XSHUT)
unnamed: C23.1, R6.2, U4.8 (INA+)
unnamed: C23.2, R5.1, U4.7 (INA-)
unnamed: C22.2, U4.6 (VBG)
unnamed: R3.2, R4.1, U4.4 (VFB)
unnamed: C21.1, U5.13 (1V8OUT)
unnamed: C15.2, U5.2 (VCP)
unnamed: TP17.1, U10.33 (IO40)
unnamed: TP18.1, U10.34 (IO41)
unnamed: TP19.1, U10.35 (IO42)
unnamed: TP20.1, U10.26 (IO45)
unnamed: TP21.1, U10.16 (IO46)
unnamed: TP22.1, U10.24 (IO47)
unnamed: TP23.1, U10.25 (IO48)
SCL: J7.1, J8.1, J9.1, Q2.3 (D), R14.2, R26.1, TP5.1, U8.1 (SCL), U10.31 (IO38)
SCL_2.8: Q2.2 (S), R23.1, U3.10 (SCL)
SDA: J7.2, J8.2, J9.2, Q3.3 (D), R13.2, R27.1, TP4.1, U8.4 (SDA), U10.32 (IO39)
SDA_2.8: Q3.2 (S), R24.1, U3.9 (SDA)

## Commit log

2023-10-25 Added thermostat demo UI
2023-10-25 Added shade UI demo
2023-10-27 added lights demo
2023-10-27 updated demos
2023-10-30 added menu demo
2023-11-01 Added PCB variant with esp32s3 and cp2102
2023-11-01 added settings page
2023-11-01 Added menu, music and apps concept
2023-11-01 added wifi
2023-11-01 update color of apps
2023-11-01 fixed bugs
2023-11-04 added apps collection
2023-11-04 moved music UI to app structure
2023-11-05 integrated apps and main flow
2023-11-07 Moved HVAC to apps
2023-11-08 Migrated to Apps concept 100%
2023-11-11 wip new display
2023-11-11 Added printer chamber temp UI
2023-11-11 wip: MQTT support
2023-11-11 wip climate app mqtt
2023-11-12 updated mqtt integration
2023-11-14 Adjusted MQTT and small fixes
2023-11-15 wip: apps factory
2023-11-19 re-routed things
2023-11-19 updated screen PCB
2023-11-19 silkscreen fixes
2023-11-20 run DRC
2023-11-22 working on a panel, run DRC for base pcb
2023-11-24 minor changes for PCBs order
2023-11-25 wip iboms
2023-11-26 moved apps construction to a method
2023-12-02 Updated ibom for base pcb
2023-12-02 updated ibom
2023-12-02 Revert "DevKit PCB"
2023-12-02 devkit v0.1
2023-12-02 Updated ibom links
2023-12-04 devkit pcb preview
2023-12-12 New readme file
    - introducing seedlabs
    - reworked the structure
    - filled out few sections.
2023-12-12 Proof reading, and minor correction
    - added link to Grigorii profile
    - proof read the existing text
2023-12-12 Added FAQ
    - Added question: How does the smart knob work?
    - How do I flash my smart knob?
2023-12-14 Create apps from JSON
2023-12-19 Update README.md
    Removed intro-prompt of proof-reading LLM

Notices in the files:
parts and their libraries:
Copyright 2021 Accelerated Designs. All rights reserved.
